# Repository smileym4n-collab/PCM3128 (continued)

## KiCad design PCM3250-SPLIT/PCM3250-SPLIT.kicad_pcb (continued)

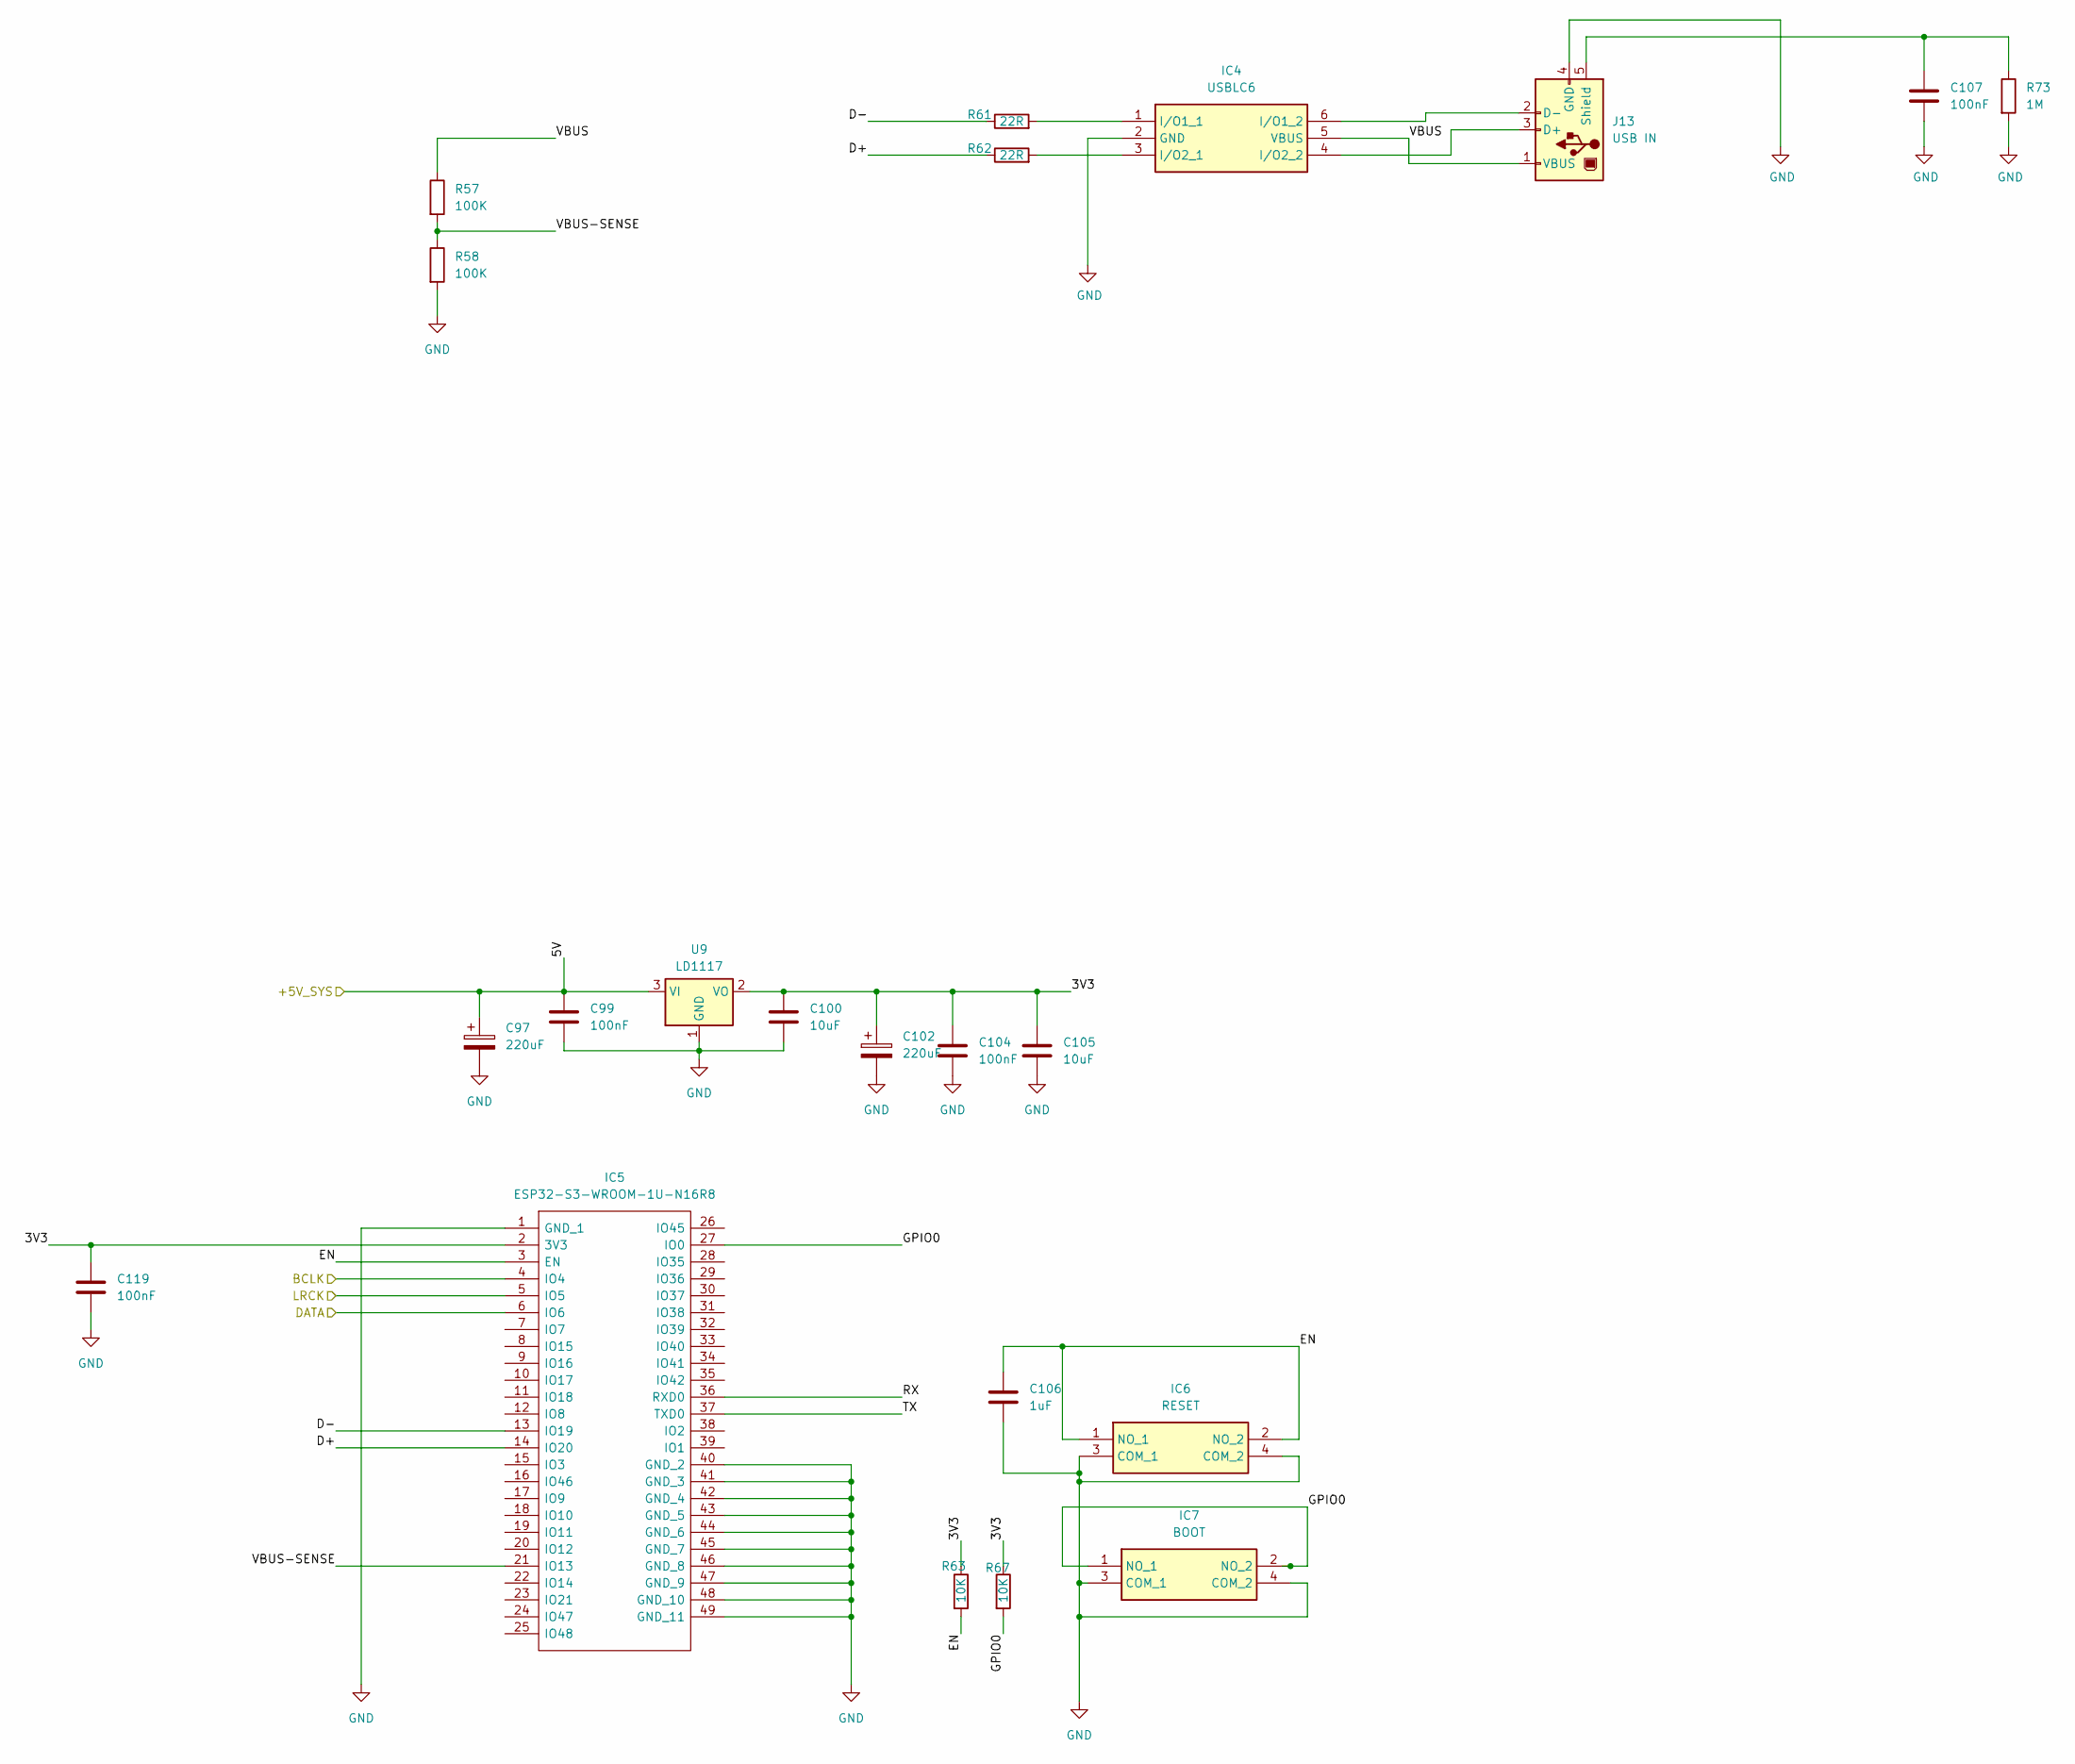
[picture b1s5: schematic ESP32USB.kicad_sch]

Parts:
C97, C102: 220uF; CP_Radial_D6.3mm_P2.50mm
C99, C104, C107, C119: 100nF; C_1206_3216Metric_Pad1.33x1.80mm_HandSolder
C100: 10uF; C_0805_2012Metric_Pad1.18x1.45mm_HandSolder
C105: 10uF; C_1206_3216Metric_Pad1.33x1.80mm_HandSolder
C106: 1uF; C_1206_3216Metric_Pad1.33x1.80mm_HandSolder
IC4: USBLC6; SOT-23-6_Handsoldering; Mouser Part Number 511-USBLC6-2SC6
IC5: ESP32-S3-WROOM-1U-N16R8; ESP32S3WROOM1UN16R8; Mouser Part Number 356-ESP32S3WM1UN16R8
IC6: RESET; TS026650BK100SCRD; Mouser Part Number 179-TS026650BK100SCR
IC7: BOOT; TS026650BK100SCRD; Mouser Part Number 179-TS026650BK100SCR
J13: USB IN; USBC
R57, R58: 100K; R_0805_2012Metric_Pad1.20x1.40mm_HandSolder
R61, R62: 22R; R_0805_2012Metric_Pad1.20x1.40mm_HandSolder
R63, R67: 10K; R_0603_1608Metric_Pad0.98x0.95mm_HandSolder
R73: 1M; R_0805_2012Metric_Pad1.20x1.40mm_HandSolder
U9: LD1117; SOT-223-3_TabPin2

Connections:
/+5V_MCU-P: C97.1, C99.1, U9.3 (VI); also elsewhere on the board
/BCLK-P: IC5.4 (IO4); also elsewhere on the board
/DATA-P: IC5.6 (IO6); also elsewhere on the board
/ESP32USB/3V3: C100.1, C102.1, C104.1, C105.1, C119.1, IC5.2 (3V3), R63.1, R67.1, U9.2 (VO)
/ESP32USB/D+: IC5.14 (IO20), R62.1
/ESP32USB/D-: IC5.13 (IO19), R61.1
/ESP32USB/EN: C106.1, IC5.3 (EN), IC6.1 (NO_1), IC6.2 (NO_2), R63.2
/ESP32USB/GPIO0: IC5.27 (IO0), IC7.1 (NO_1), IC7.2 (NO_2), R67.2
/ESP32USB/RX: IC5.36 (RXD0)
/ESP32USB/TX: IC5.37 (TXD0)
/ESP32USB/VBUS: IC4.5 (VBUS), J13.1 (VBUS), R57.1
/ESP32USB/VBUS-SENSE: IC5.21 (IO13), R57.2, R58.1
/LRCK-P: IC5.5 (IO5); also elsewhere on the board
GND: C97.2, C99.2, C100.2, C102.2, C104.2, C105.2, C106.2, C107.2, C119.2, IC4.2 (GND), IC5.1 (GND_1), IC5.40 (GND_2), IC5.41 (GND_3), IC5.42 (GND_4), IC5.43 (GND_5), IC5.44 (GND_6), IC5.45 (GND_7), IC5.46 (GND_8), IC5.47 (GND_9), IC5.48 (GND_10), IC5.49 (GND_11), IC6.3 (COM_1), IC6.4 (COM_2), IC7.3 (COM_1), IC7.4 (COM_2), J13.4 (GND), R58.2, R73.2, U9.1 (GND); also elsewhere on the board
unnamed: IC4.1 (I/O1_1), R61.2
unnamed: IC4.6 (I/O1_2), J13.2 (D-)
unnamed: IC4.3 (I/O2_1), R62.2
unnamed: IC4.4 (I/O2_2), J13.3 (D+)
unnamed: C107.1, J13.5 (Shield), R73.1

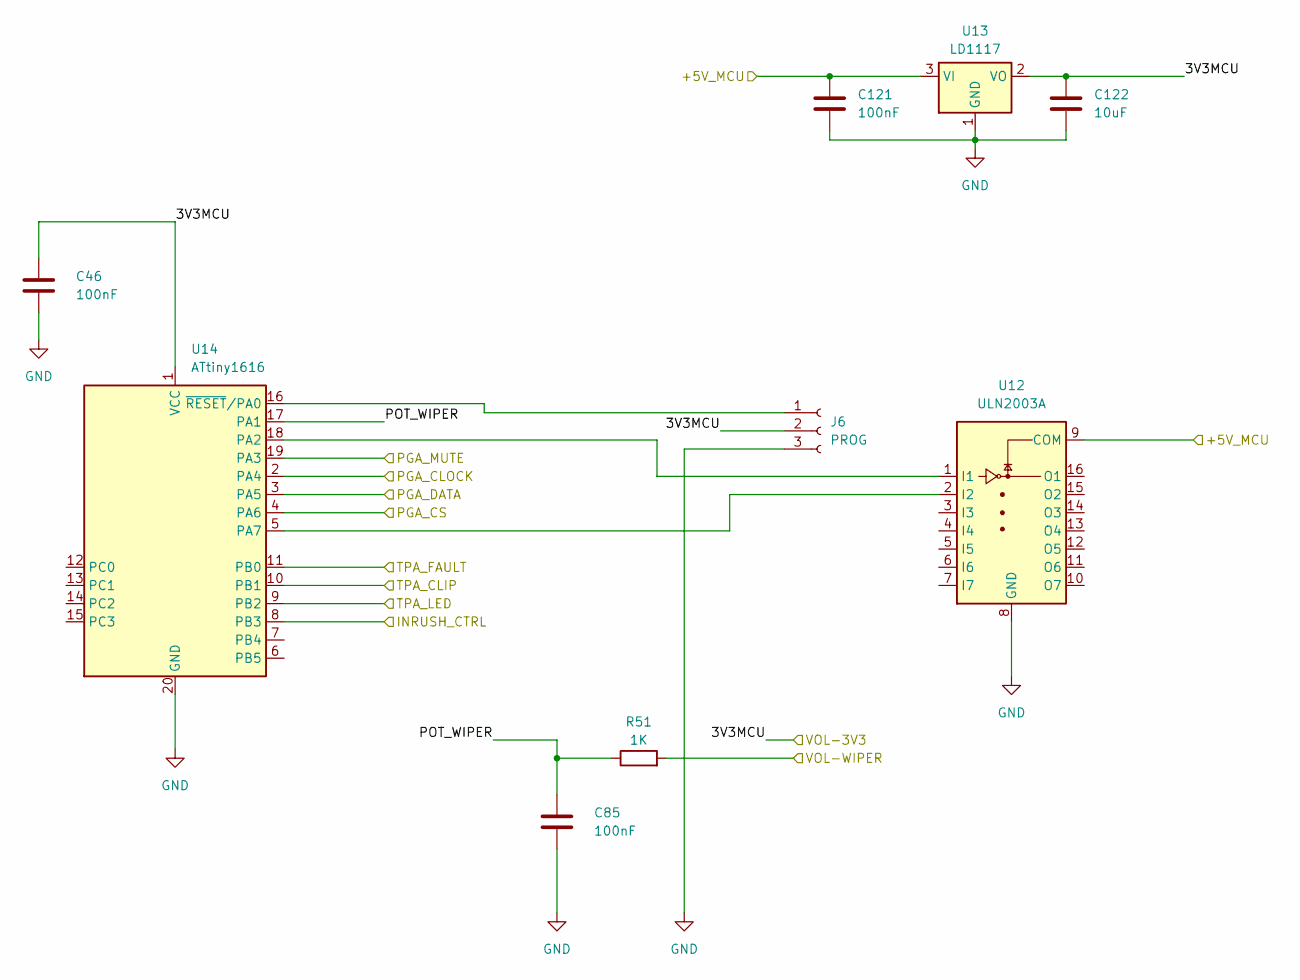
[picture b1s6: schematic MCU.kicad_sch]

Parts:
C46, C85, C121: 100nF; C_1206_3216Metric_Pad1.33x1.80mm_HandSolder
C122: 10uF; C_0805_2012Metric_Pad1.18x1.45mm_HandSolder
J6: PROG; JST_XH_B3B-XH-A_1x03_P2.50mm_Vertical
R51: 1K; R_0805_2012Metric_Pad1.20x1.40mm_HandSolder
U12: ULN2003A; SOIC-16_3.9x9.9mm_P1.27mm
U13: LD1117; SOT-223-3_TabPin2
U14: ATtiny1616; SOIC-20W_7.5x12.8mm_P1.27mm

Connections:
/+5V_MCU-A: C121.1, U12.9 (COM), U13.3 (VI); also elsewhere on the board
/INRUSH_CTRL-A: U14.8 (PB3); also elsewhere on the board
/MCU/PGA_CLOCK: U14.2 (PA4); also elsewhere on the board
/MCU/PGA_CS: U14.4 (PA6); also elsewhere on the board
/MCU/PGA_DATA: U14.3 (PA5); also elsewhere on the board
/MCU/PGA_MUTE: U14.19 (PA3); also elsewhere on the board
/MCU/POT_WIPER: C85.1, R51.1, U14.17 (PA1)
/MCU/TPA_CLIP: U14.10 (PB1)
/MCU/TPA_FAULT: U14.11 (PB0)
/MCU/TPA_LED: U14.9 (PB2)
/VOL-3V3: C46.1, C122.1, J6.2, U13.2 (VO), U14.1 (VCC); also elsewhere on the board
/VOL-WIPER: R51.2; also elsewhere on the board
GND: C46.2, C85.2, C121.2, C122.2, J6.3, U12.8 (GND), U13.1 (GND), U14.20 (GND); also elsewhere on the board
unnamed: J6.1, U14.16 (~RESET/PA0)
unnamed: U12.1 (I1), U14.18 (PA2)
unnamed: U12.2 (I2), U14.5 (PA7)

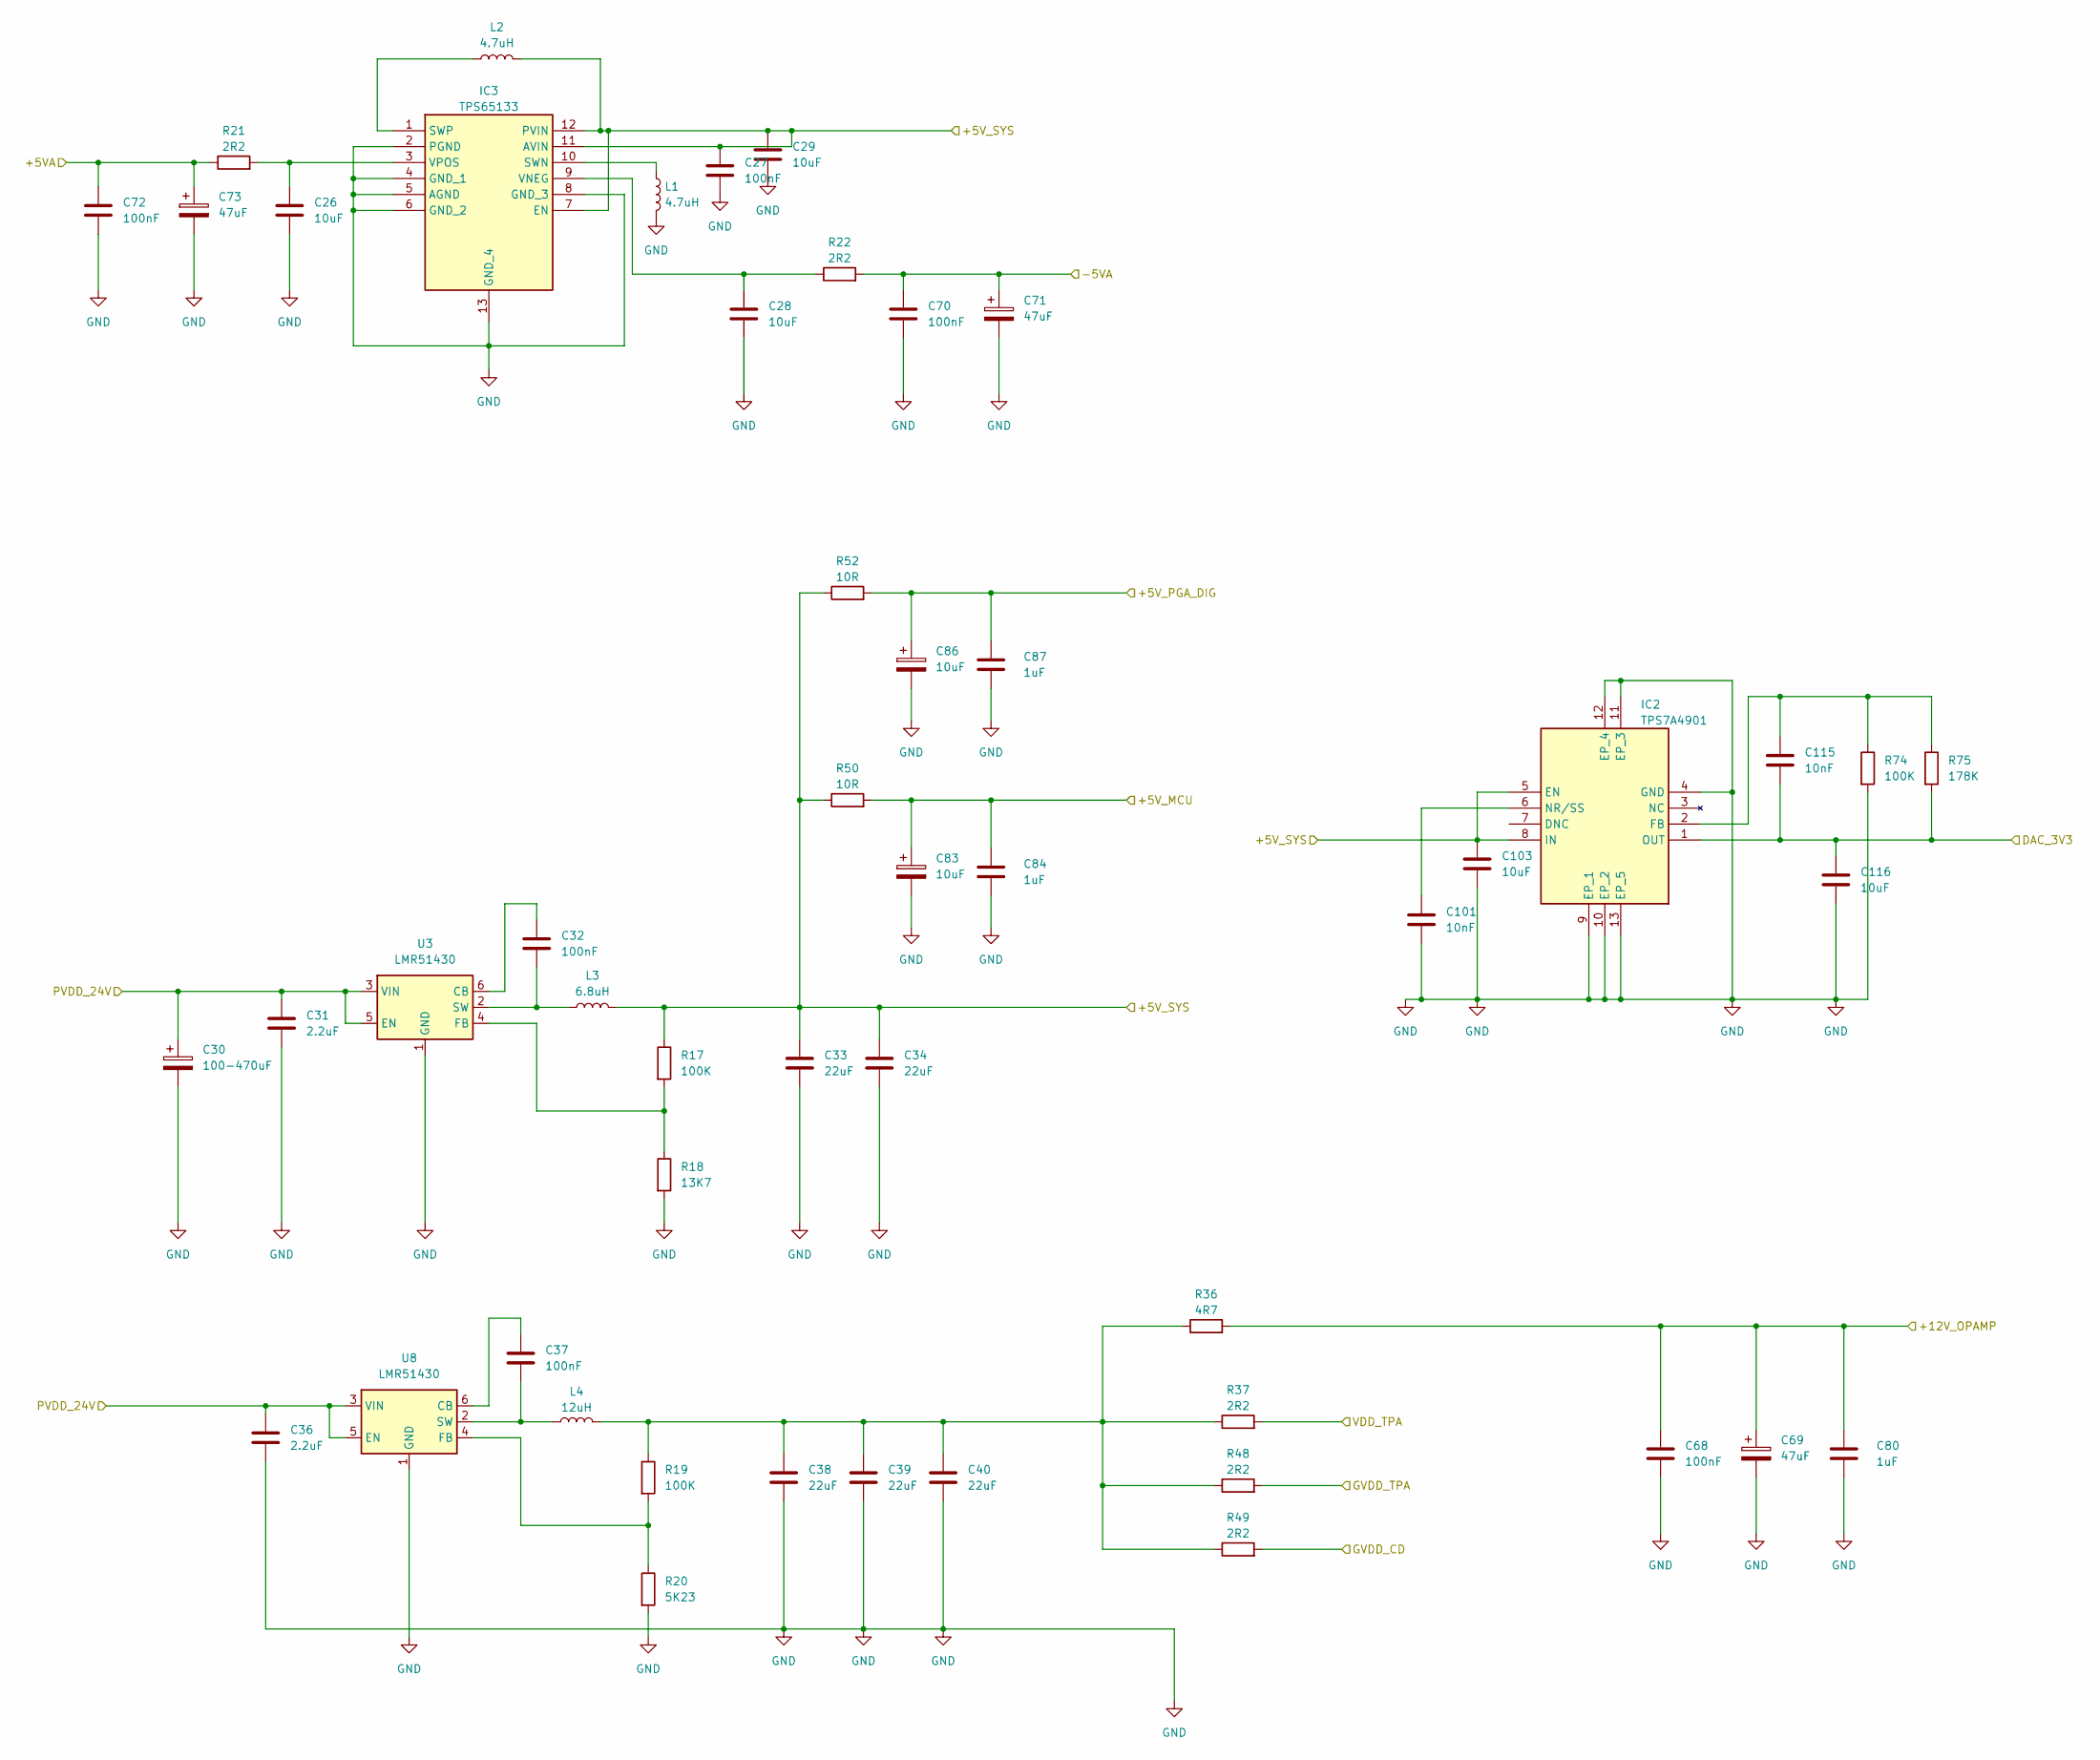
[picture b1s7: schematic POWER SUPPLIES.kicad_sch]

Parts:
C26, C28, C29: 10uF; C_0805_2012Metric_Pad1.18x1.45mm_HandSolder
C27, C32, C37, C68, C70, C72: 100nF; C_1206_3216Metric_Pad1.33x1.80mm_HandSolder
C30: 100-470uF; CP_Radial_D8.0mm_P3.50mm
C31, C36: 2.2uF; C_0805_2012Metric_Pad1.18x1.45mm_HandSolder
C33, C34, C38, C39, C40: 22uF; C_1206_3216Metric_Pad1.33x1.80mm_HandSolder
C69, C71, C73: 47uF; CP_Radial_D5.0mm_P2.50mm
C80, C84, C87: 1uF; C_1206_3216Metric_Pad1.33x1.80mm_HandSolder
C83, C86: 10uF; CP_Radial_D4.0mm_P2.00mm
C101, C115: 10nF; C_0805_2012Metric_Pad1.18x1.45mm_HandSolder
C103, C116: 10uF; C_1206_3216Metric_Pad1.33x1.80mm_HandSolder
IC2: TPS7A4901; TPS7A4901DRBR; Mouser Part Number 595-TPS7A4901DRBR
IC3: TPS65133; SON45P300X300X80-13N-D; Mouser Part Number 595-TPS65133DPDR
L1, L2: 4.7uH; L_1008_2520Metric_Pad1.43x2.20mm_HandSolder
L3: 6.8uH; SRP6030WA-6R8M
L4: 12uH; SRP6030WA-6R8M
R17, R19, R74: 100K; R_0805_2012Metric_Pad1.20x1.40mm_HandSolder
R18: 13K7; R_0805_2012Metric_Pad1.20x1.40mm_HandSolder
R20: 5K23; R_0805_2012Metric_Pad1.20x1.40mm_HandSolder
R21, R22: 2R2; R_0805_2012Metric_Pad1.20x1.40mm_HandSolder
R36: 4R7; R_0805_2012Metric_Pad1.20x1.40mm_HandSolder
R37, R48, R49: 2R2; R_1206_3216Metric_Pad1.30x1.75mm_HandSolder
R50, R52: 10R; R_0805_2012Metric_Pad1.20x1.40mm_HandSolder
R75: 178K; R_0805_2012Metric_Pad1.20x1.40mm_HandSolder
U3, U8: LMR51430; SOT-23-6_Handsoldering

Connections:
/+5VA-P: C72.1, C73.1, R21.1; also elsewhere on the board
/+5V_MCU-P: C83.1, C84.1, R50.2; also elsewhere on the board
/+5V_PGA_DIG-P: C86.1, C87.1, R52.2; also elsewhere on the board
/+12V_OPAMP: C68.1, C69.1, C80.1, R36.2; also elsewhere on the board
/-5VA-P: C70.1, C71.1, R22.2; also elsewhere on the board
/POWER SUPPLIES/+5V_SYS: C27.1, C29.1, C33.1, C34.1, C103.2, IC2.5 (EN), IC2.8 (IN), IC3.7 (EN), IC3.11 (AVIN), IC3.12 (PVIN), L2.2, L3.2, R17.1, R50.1, R52.1
/POWER SUPPLIES/GVDD_CD: R49.2
/POWER SUPPLIES/GVDD_TPA: R48.2
/POWER SUPPLIES/VDD_TPA: R37.2
/PVDD_24V: C30.1, C31.1, C36.1, U3.3 (VIN), U3.5 (EN), U8.3 (VIN), U8.5 (EN); also elsewhere on the board
GND: C26.2, C27.2, C28.2, C29.2, C30.2, C31.2, C33.2, C34.2, C36.2, C38.2, C39.2, C40.2, C68.2, C69.2, C70.2, C71.2, C72.2, C73.2, C80.2, C83.2, C84.2, C86.2, C87.2, C101.2, C103.1, C116.1, IC2.4 (GND), IC2.9 (EP_1), IC2.10 (EP_2), IC2.11 (EP_3), IC2.12 (EP_4), IC2.13 (EP_5), IC3.2 (PGND), IC3.4 (GND_1), IC3.5 (AGND), IC3.6 (GND_2), IC3.8 (GND_3), IC3.13 (GND_4), L1.2, R18.2, R20.2, R74.2, U3.1 (GND), U8.1 (GND); also elsewhere on the board
unnamed: C38.1, C39.1, C40.1, L4.2, R19.1, R36.1, R37.1, R48.1, R49.1
unnamed 85: C115.1, IC2.2 (FB), R74.1, R75.1; also elsewhere on the board
unnamed: C101.1, IC2.6 (NR/SS)
unnamed: IC3.10 (SWN), L1.1
unnamed: IC3.1 (SWP), L2.1
unnamed: C28.1, IC3.9 (VNEG), R22.1
unnamed: C26.1, IC3.3 (VPOS), R21.2
unnamed: C32.1, U3.6 (CB)
unnamed: R17.2, R18.1, U3.4 (FB)
unnamed: C32.2, L3.1, U3.2 (SW)
unnamed: C37.1, U8.6 (CB)
unnamed: R19.2, R20.1, U8.4 (FB)
unnamed: C37.2, L4.1, U8.2 (SW)

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
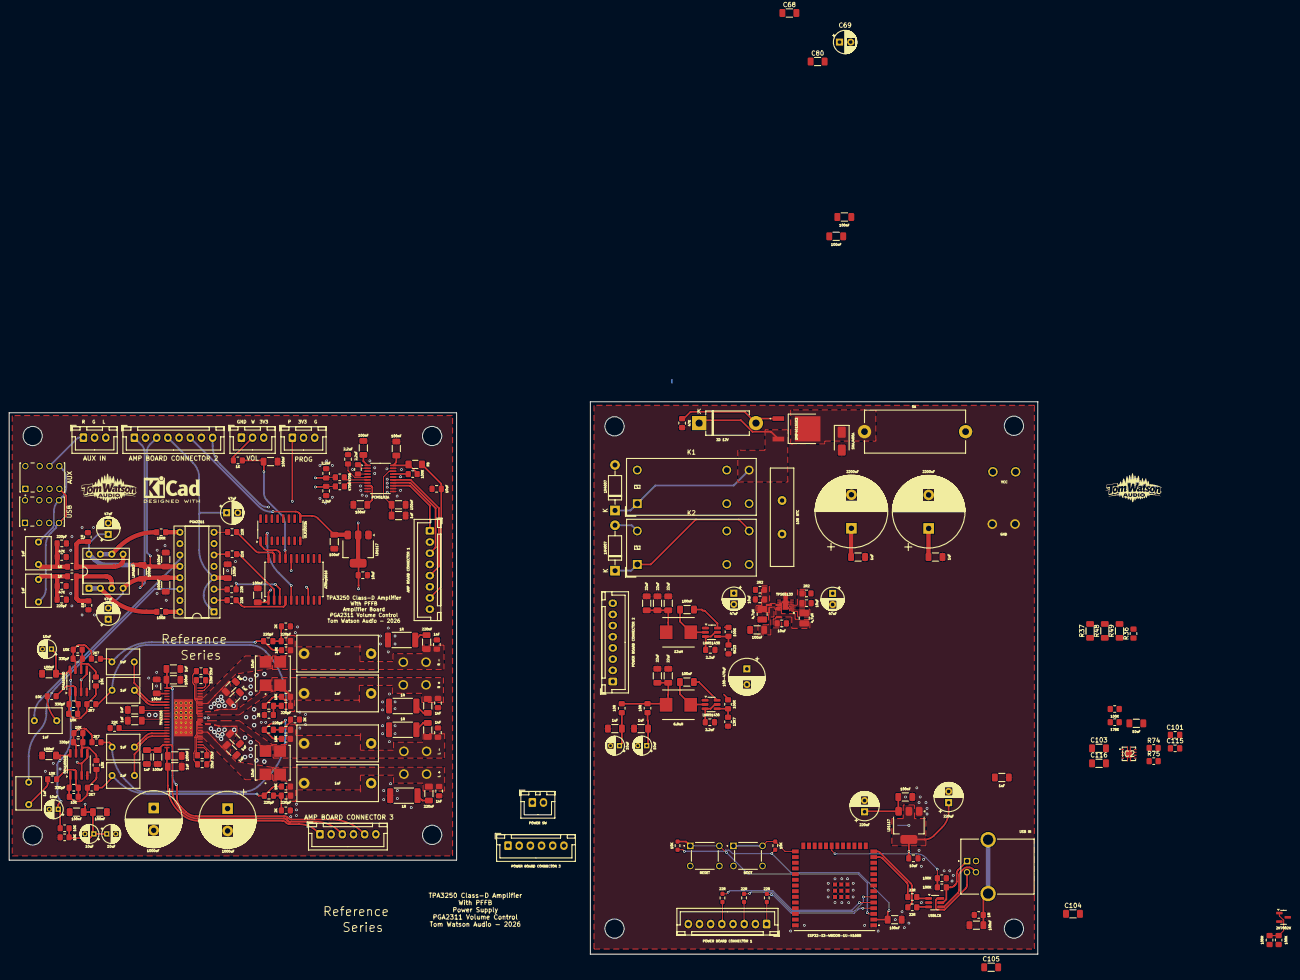
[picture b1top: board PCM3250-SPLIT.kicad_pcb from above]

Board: 4 copper layers, 229.9 x 123.5 mm, 259 parts (0 on the bottom side), 143 nets.

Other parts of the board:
C116#2: 10uF; C_1206_3216Metric_Pad1.33x1.80mm_HandSolder
R74#2: 100K; R_0805_2012Metric_Pad1.20x1.40mm_HandSolder
R75#2: 178K; R_0805_2012Metric_Pad1.20x1.40mm_HandSolder

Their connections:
GND: C116#2.1, R74#2.2; also elsewhere on the board
unnamed 85: R74#2.1, R75#2.1; also elsewhere on the board

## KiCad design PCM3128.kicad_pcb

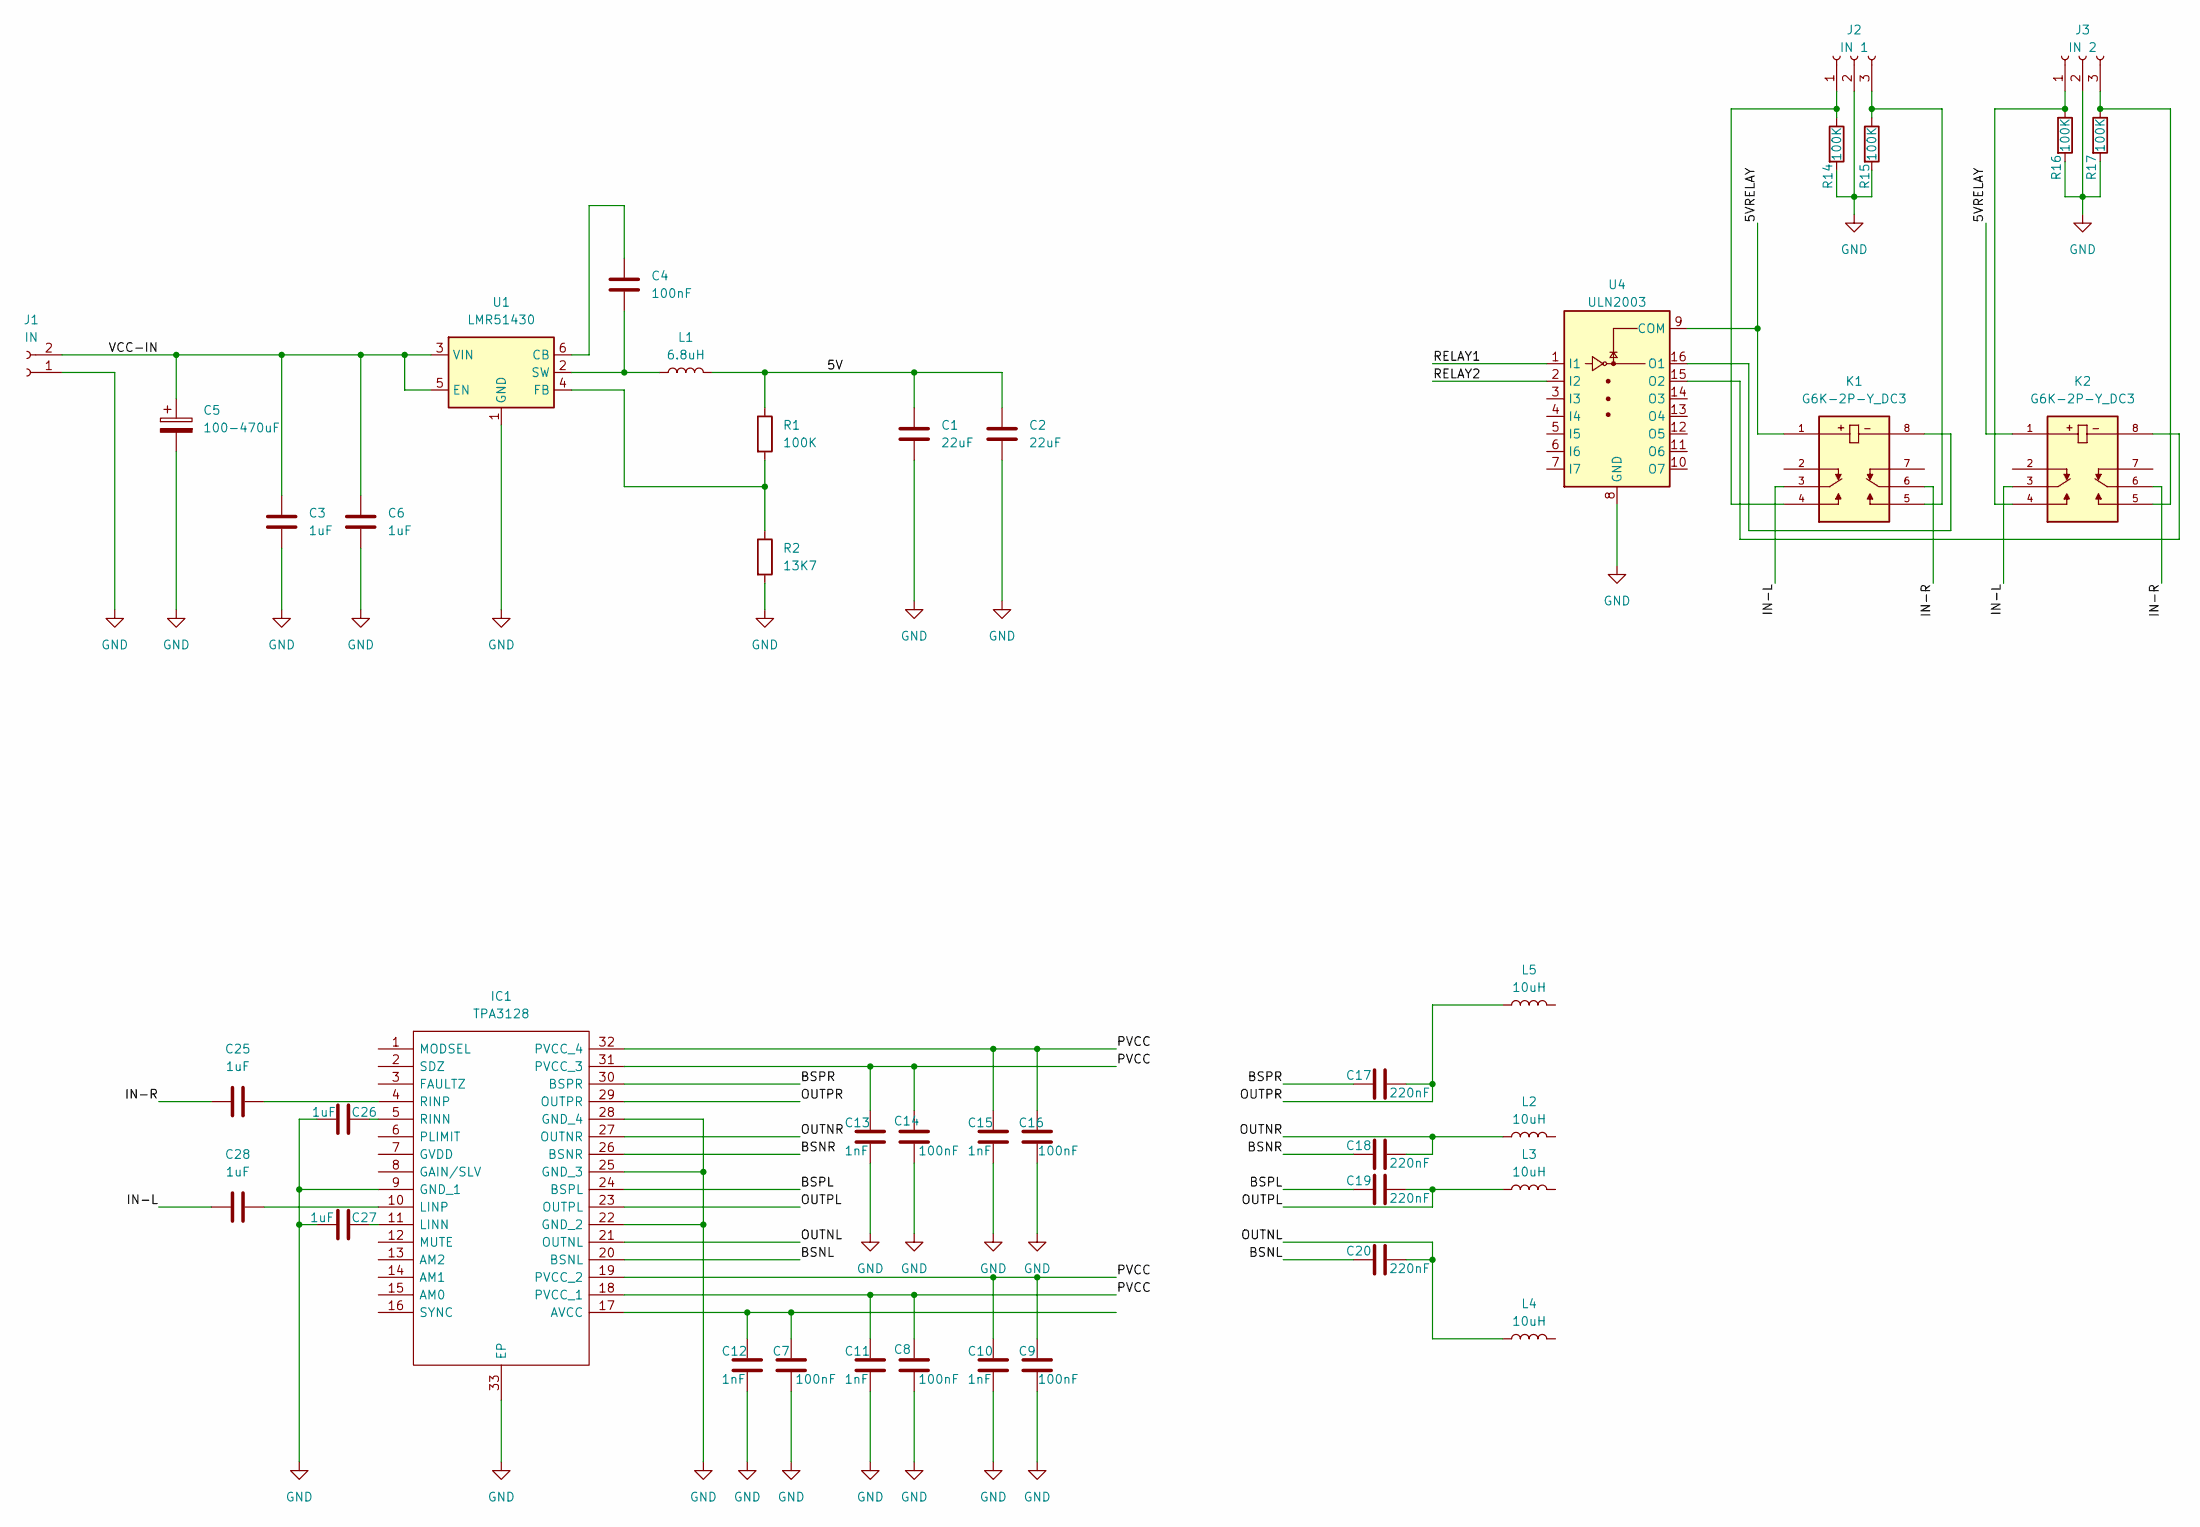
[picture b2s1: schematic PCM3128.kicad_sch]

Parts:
C1, C2: 22uF; C_1206_3216Metric_Pad1.33x1.80mm_HandSolder
C3, C6: 1uF; C_1206_3216Metric_Pad1.33x1.80mm_HandSolder
C4, C7, C8, C9, C14, C16: 100nF; C_1206_3216Metric_Pad1.33x1.80mm_HandSolder
C5: 100-470uF; CP_Radial_D8.0mm_P3.50mm
C10, C11, C12, C13, C15: 1nF; C_0603_1608Metric_Pad1.08x0.95mm_HandSolder
C17, C18, C19, C20: 220nF; C_Rect_L7.2mm_W2.5mm_P5.00mm_FKS2_FKP2_MKS2_MKP2
C25, C26, C27, C28: 1uF; C_Rect_L7.2mm_W5.5mm_P5.00mm_FKS2_FKP2_MKS2_MKP2
IC1: TPA3128; Mouser Part Number 595-TPA3128D2DAPR
J1: IN; JST_XH_B2B-XH-A_1x02_P2.50mm_Vertical
J2: IN 1; JST_XH_B3B-XH-A_1x03_P2.50mm_Vertical
J3: IN 2; JST_XH_B3B-XH-A_1x03_P2.50mm_Vertical
K1, K2: G6K-2P-Y_DC3; RELAY_G6K-2P-Y_DC3; PARTREV K106-E1-11
L1: 6.8uH; SRP6030WA-6R8M
L2, L3, L4, L5: 10uH; ETQP5M100YFC
R1, R14, R15, R16, R17: 100K; R_0805_2012Metric_Pad1.20x1.40mm_HandSolder
R2: 13K7; R_0805_2012Metric_Pad1.20x1.40mm_HandSolder
U1: LMR51430; SOT-23-6_Handsoldering
U4: ULN2003; SOIC-16_3.9x9.9mm_P1.27mm

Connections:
/5V: C1.1, C2.1, L1.2, R1.1
/5VRELAY: K1.1, K2.1, U4.9 (COM)
/BSNL: C20.1, IC1.20 (BSNL)
/BSNR: C18.1, IC1.26 (BSNR)
/BSPL: C19.1, IC1.24 (BSPL)
/BSPR: C17.1, IC1.30 (BSPR)
/IN-L: C28.1, K1.3, K2.3
/IN-R: C25.1, K1.6, K2.6
/OUTNL: C20.2, IC1.21 (OUTNL), L4.1
/OUTNR: C18.2, IC1.27 (OUTNR), L2.1
/OUTPL: C19.2, IC1.23 (OUTPL), L3.1
/OUTPR: C17.2, IC1.29 (OUTPR), L5.1
/PVCC: C8.1, C9.1, C10.1, C11.1, C13.1, C14.1, C15.1, C16.1, IC1.18 (PVCC_1), IC1.19 (PVCC_2), IC1.31 (PVCC_3), IC1.32 (PVCC_4)
/RELAY1: U4.1 (I1)
/RELAY2: U4.2 (I2)
/VCC-IN: C3.1, C5.1, C6.1, J1.2, U1.3 (VIN), U1.5 (EN)
GND: C1.2, C2.2, C3.2, C5.2, C6.2, C7.2, C8.2, C9.2, C10.2, C11.2, C12.2, C13.2, C14.2, C15.2, C16.2, C26.1, C27.1, IC1.9 (GND_1), IC1.22 (GND_2), IC1.25 (GND_3), IC1.28 (GND_4), IC1.33 (EP), J1.1, J2.2, J3.2, R2.2, R14.2, R15.2, R16.2, R17.2, U1.1 (GND), U4.8 (GND)
unnamed: C7.1, C12.1, IC1.17 (AVCC)
unnamed: C27.2, IC1.11 (LINN)
unnamed: C28.2, IC1.10 (LINP)
unnamed: C26.2, IC1.5 (RINN)
unnamed: C25.2, IC1.4 (RINP)
unnamed: J2.1, K1.4, R14.1
unnamed: J2.3, K1.5, R15.1
unnamed: J3.1, K2.4, R16.1
unnamed: J3.3, K2.5, R17.1
unnamed: C4.1, U1.6 (CB)
unnamed: R1.2, R2.1, U1.4 (FB)
unnamed: C4.2, L1.1, U1.2 (SW)
unnamed: K1.8, U4.16 (O1)
unnamed: K2.8, U4.15 (O2)

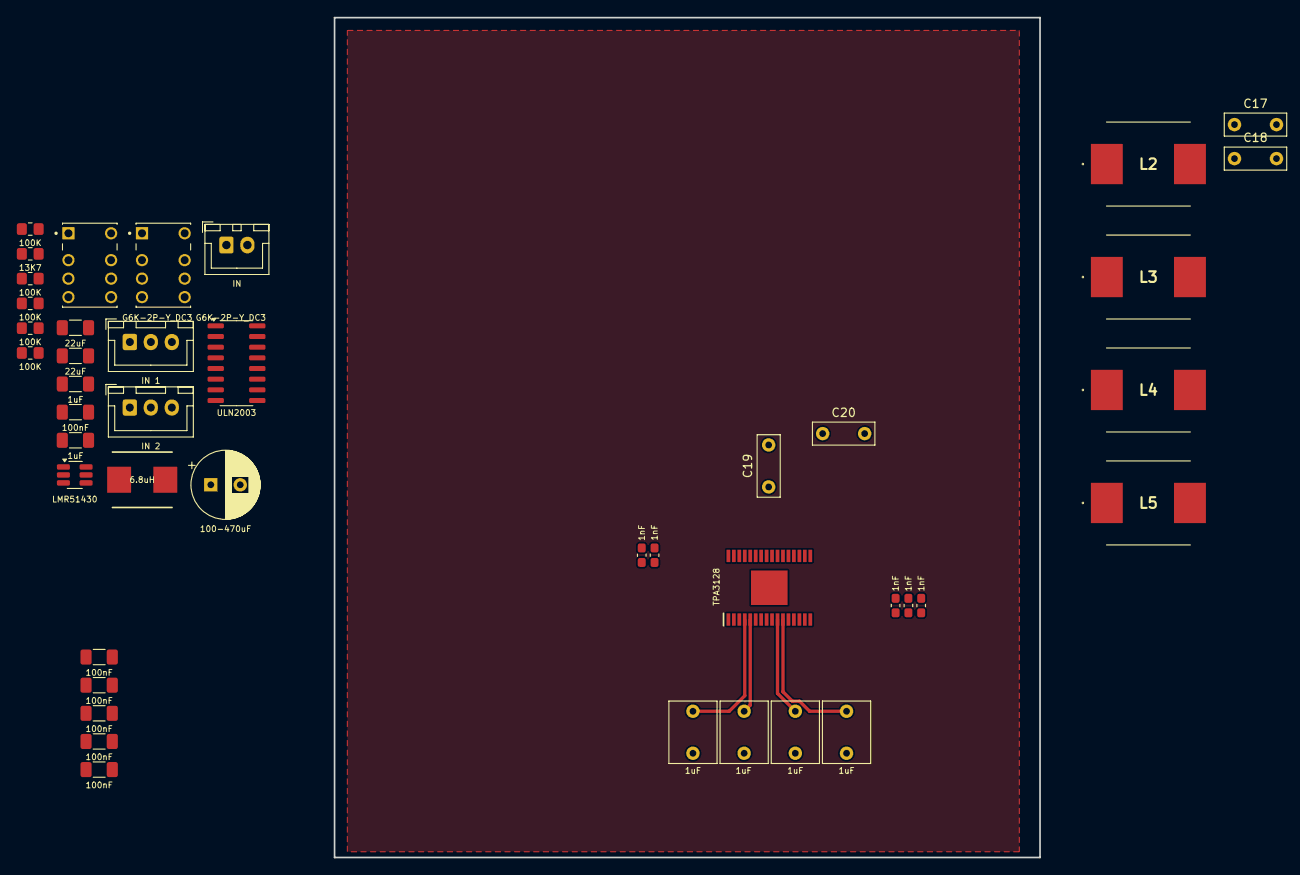
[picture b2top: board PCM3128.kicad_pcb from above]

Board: 2 copper layers, 84.0 x 100.0 mm, 43 parts (0 on the bottom side), 29 nets.
